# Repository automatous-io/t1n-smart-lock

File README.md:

# T1N Smart Lock

The T1N Smart Lock is an open source Matter over Thread device designed
for the 2005 Dodge Sprinter 2500 (T1N chassis). It adds what the van never
had: lock and unlock from your iPhone, lock state you can see at a glance,
and a sensor for any door left ajar. It does this without driving the lock
motors directly or replacing the factory module. The factory keys and key fob
keep working exactly as before.

The factory service manual identifies the wires, but does not describe reading
the lock-state LEDs, using the central timer module (CTM) rail to tell when the
van is asleep, or pulsing the locks once or twice depending on state. That approach
is the idea behind this project. Every signal and timing it depends on was worked out
by hand, with a multimeter at the back of the master door lock switch and a long stretch
of testing in the van. The manual gives you the pinout; it does not give you the design.

This device reports observed reality, not commanded state. So your app reflects what
the van actually did, not just what it was told to do.

<p align="center">
  
  <br>
  <sub>Click to watch a short demo: opening/closing driver door, then locking and unlocking, with the master lock switch LEDs and Apple Home following each change.</sub>
</p>

It is built primarily for offgrid and vanlife use. It can run from either the
van's starter battery or a house/leisure battery; see
[INSTALL.md](docs/INSTALL.md#choosing-a-12v-source) for the tradeoffs.
It tolerates a noisy electrical environment including engine-on
conditions, and is a low-power Matter device so the power budget stays
small. It is local-first: it pairs and operates over Thread directly
from an iPhone 15 Pro or newer model featuring a Thread radio, and also
works through any compatible Thread Border Router for use in Apple Home,
Home Assistant, Google Home, or Alexa.

## How it works

The board is a small carrier for a Seeed Studio XIAO ESP32-C6, which
provides the Thread radio and runs the firmware. A transistor pulses
the factory master lock line, two optocouplers read the center console
switch LEDs without loading them, and a comparator turns the CTM sense
line into clean edges for sleep detection. The only connection to the
van is five wires tapped at the back of the master door lock switch,
landed on the board's five-position terminal block.

In your Matter app the device appears as a door lock plus two contact
sensors, one for the driver side and one for the passenger, cargo, and
rear doors. For the full architecture see [FIRMWARE.md](docs/FIRMWARE.md).

<p align="center">

  <br>
  <sub>The same lock in Apple Home and Home Assistant. Matter is multi-admin, so it pairs to more than one ecosystem at once (see <a href="docs/INSTALL.md#commission-the-device">Commission the device</a>).</sub>
</p>

## Documentation

Everything is in [`docs/`](docs/). A typical path is to read SAFETY
first, build the board and enclosure, flash the firmware, then
commission and install it in the van.

| Document | What's in it |
|---|---|
| [FIRMWARE.md](docs/FIRMWARE.md) | firmware architecture and behavior |
| [HARDWARE.md](docs/HARDWARE.md) | PCB design, BOM, and ordering |
| [ENCLOSURE.md](docs/ENCLOSURE.md) | 3D printed enclosure |
| [BUILDING.md](docs/BUILDING.md) | building and flashing the firmware |
| [INSTALL.md](docs/INSTALL.md) | commissioning and van installation |
| [SAFETY.md](docs/SAFETY.md) | electrical and operational safety |
| [CERTIFICATION.md](docs/CERTIFICATION.md) | Matter/Thread certification status |
| [CONTRIBUTING.md](docs/CONTRIBUTING.md) | how to contribute |
| [LICENSING.md](docs/LICENSING.md) | license terms |

## Repository layout

| Path | Contents |
|---|---|
| [`firmware/`](firmware/) | C++ application on ESP-IDF (C/C++), source in `main/` |
| [`hardware/`](hardware/) | KiCad project, schematic, and gerbers |
| [`enclosure/`](enclosure/) | 3D printed enclosure model files |
| [`docs/`](docs/) | all project documentation |

## Status and compatibility

This is v1.0 of a personal project, developed and
tested by a single maintainer. It is an uncertified Matter device that
uses public test credentials, which is normal for a self-built device
and explained in [CERTIFICATION.md](docs/CERTIFICATION.md). Response
times on issues vary.

The firmware was developed and verified against one vehicle.
Compatibility with any other year, market, or trim is unconfirmed. If
you run it on a different T1N, a compatibility report is welcome. The
list below will grow as verified reports come in.

| Vehicle | Market | Status | Notes |
|---|---|---|---|
| 2005 Dodge Sprinter 2500 | North America | Verified | Reference build |

Firmware, PCB, and enclosure version history, and which revisions are
validated to work together, are recorded in [CHANGELOG.md](CHANGELOG.md).

## Safety

Installing this device modifies your vehicle's electrical system and
interfaces with the factory locking system. Wiring errors can damage
the CTM or the board. Read [SAFETY.md](docs/SAFETY.md) before building
or installing anything.

## Other projects from Automatous

| Project | What it is |
|---|---|
| [shelly-1-gen4-matter-thread](https://github.com/automatous-io/shelly-1-gen4-matter-thread) | open source Matter over Thread firmware for the Shelly 1 Gen4 |

## Licensing

This repository is multi-licensed. The firmware in `firmware/` is
[Apache 2.0](firmware/LICENSE.txt). The hardware in `hardware/` and the
enclosure in `enclosure/` are both CC BY 4.0
([hardware](hardware/LICENSE.txt), [enclosure](enclosure/LICENSE.txt)).
Both are open source. Use,
modification, sharing, and commercial use are all allowed, with
attribution. See [LICENSING.md](docs/LICENSING.md) for the plain
language version.

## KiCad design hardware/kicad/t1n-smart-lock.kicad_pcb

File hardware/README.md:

# Hardware

KiCad design files and gerbers for the T1N Smart Lock PCB.
Licensed under [CC BY 4.0](LICENSE.txt).

See [HARDWARE.md](../docs/HARDWARE.md) for design notes, BOM, and
ordering instructions.

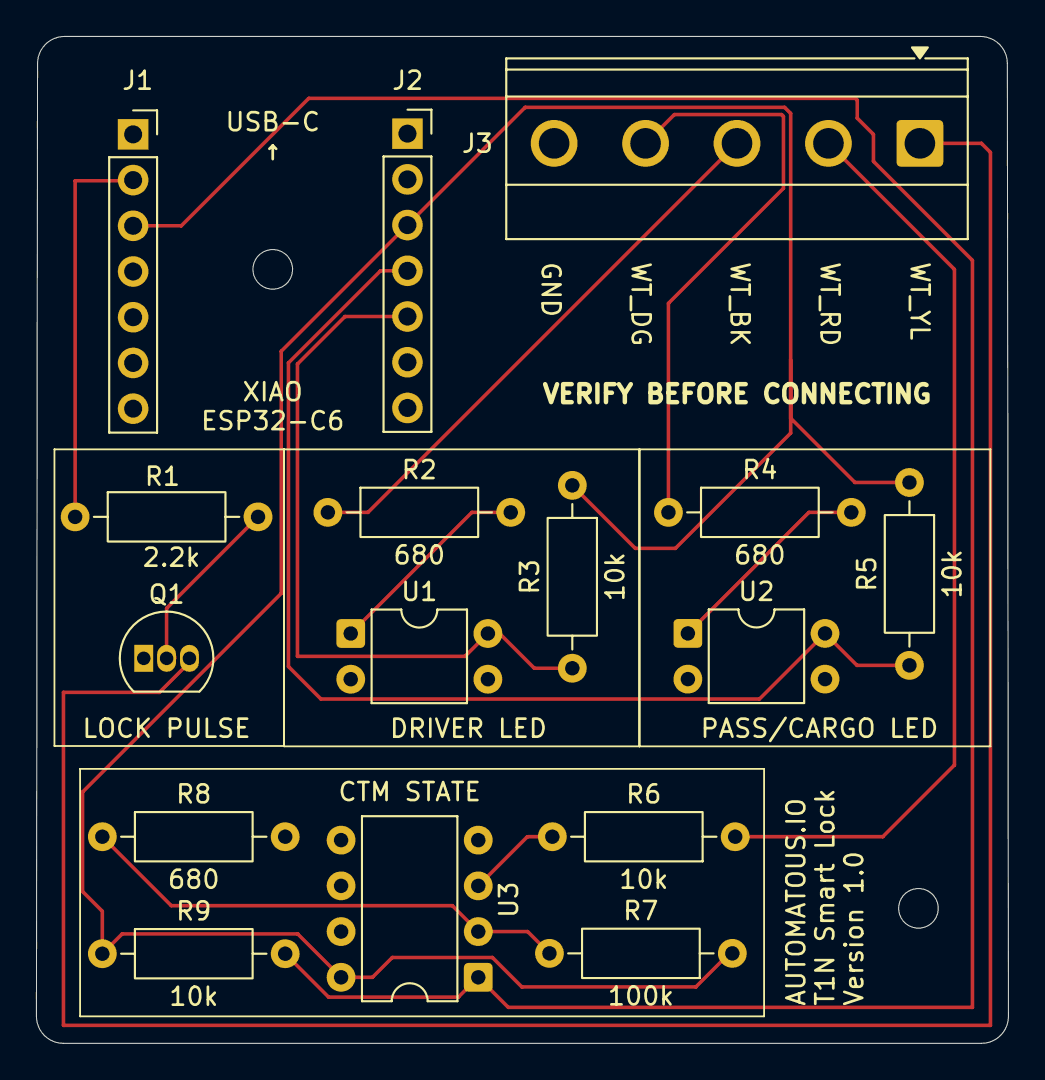
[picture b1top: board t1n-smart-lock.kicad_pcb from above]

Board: 2 copper layers, 54.0 x 55.9 mm, 18 parts (0 on the bottom side), 15 nets.

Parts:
H1, H2: MountingHole_2.2mm_M2
J1, J2: Conn_01x07_Socket; PinSocket_1x07_P2.54mm_Vertical
J3: TerminalBlock_Phoenix_MKDS-1,5-5-5.08_1x05_P5.08mm_Horizont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
Q1: LOCK PULSE; TO-92_Inline
R1: 2.2k; R_Axial_DIN0207_L6.3mm_D2.5mm_P10.16mm_Horizontal
R2, R4, R8: 680; R_Axial_DIN0207_L6.3mm_D2.5mm_P10.16mm_Horizontal
R3, R5, R6, R9: 10k; R_Axial_DIN0207_L6.3mm_D2.5mm_P10.16mm_Horizontal
R7: 100k; R_Axial_DIN0207_L6.3mm_D2.5mm_P10.16mm_Horizontal
U1: DRIVER LED; DIP-4_W7.62mm
U2: PASS/CARGO LED; DIP-4_W7.62mm
U3: CTM STATE; DIP-8_W7.62mm

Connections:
+3V3: J2.3, R3.1, R5.1, R7.1, R9.1, U3.8 (V+)
/GPIO1: J1.2, R1.1
/GPIO2: J1.3, R9.2, U3.1
/GPIO18: J2.4, R5.2, U2.4
/GPIO20: J2.5, R3.2, U1.4
/WT_BK: J3.3, R2.1
/WT_DG: J3.4, R4.1
/WT_RD: J3.2, R6.1
/WT_YL: J3.1, Q1.3 (C)
GND: J2.2, J3.5, Q1.1 (E), R8.2, U1.2, U1.3, U2.2, U2.3, U3.4 (V-)
unnamed: Q1.2 (B), R1.2
unnamed: R2.2, U1.1
unnamed: R4.2, U2.1
unnamed: R6.2, U3.3 (+)
unnamed: R7.2, R8.1, U3.2 (-)

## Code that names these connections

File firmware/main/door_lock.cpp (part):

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// example boilerplate in door_lock_manager.cpp).
//
// GPIO ownership lives in dedicated modules:
//   GPIO1  (lock pulse output)                   -> lock_pulse.cpp
//   GPIO2  (CTM sleep detect)                    -> ctm_state.cpp
//   GPIO18 (master door lock switch pax LED)     -> doors.cpp
//   GPIO20 (master door lock switch driver LED)  -> doors.cpp
//
// This file owns no hardware directly.
//
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
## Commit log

2026-06-12 Initial public release of the T1N Smart Lock firmware, hardware (KiCad source, schematic, gerbers), 3D-printed enclosure, and full documentation. Open source Matter over Thread smart lock for the 200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
2026-06-14 "Firmware 1.0.1: bump esp_matter 1.4.2~2 → 1.5.0, fix contact sensors esp_matter 1.5 makes BooleanState a code driven cluster, so attribute::update() on StateValue returns ESP_ERR_NOT_SUPPORTED and t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

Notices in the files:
firmware/main/door_lock.cpp:
Copyright 2025-2026 AUTOMATOUS.IO
Portions derived from Espressif esp-matter examples,
originally released into the public domain / CC0.
Licensed under the Apache License, Version 2.0 (the "License");
